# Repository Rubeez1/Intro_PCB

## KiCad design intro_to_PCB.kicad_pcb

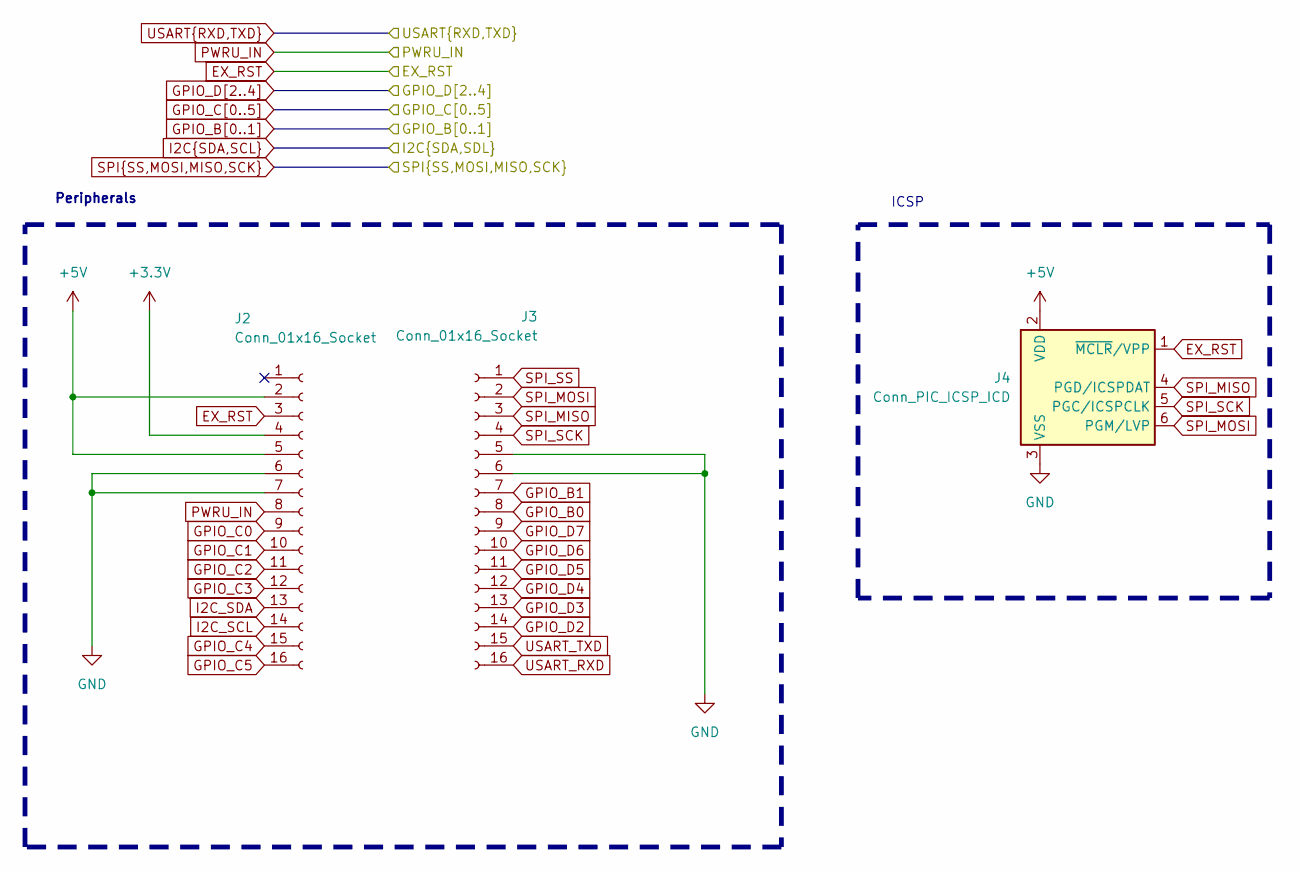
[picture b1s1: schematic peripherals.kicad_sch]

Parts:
J2, J3: Conn_01x16_Socket; PinHeader_1x16_P2.54mm_Vertical
J4: Conn_PIC_ICSP_ICD; PinHeader_2x03_P2.54mm_Vertical

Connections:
+3.3V: J2.4; also elsewhere on the board
+5V: J2.2, J2.5, J4.2 (VDD); also elsewhere on the board
EX_RST: J2.3, J4.1 (~MCLR/VPP); also elsewhere on the board
GND: J2.6, J2.7, J3.5, J3.6, J4.3 (VSS); also elsewhere on the board
GPIO_B0: J3.8; also elsewhere on the board
GPIO_B1: J3.7; also elsewhere on the board
GPIO_C0: J2.9; also elsewhere on the board
GPIO_C1: J2.10; also elsewhere on the board
GPIO_C2: J2.11; also elsewhere on the board
GPIO_C3: J2.12; also elsewhere on the board
GPIO_C4: J2.15; also elsewhere on the board
GPIO_C5: J2.16; also elsewhere on the board
GPIO_D2: J3.14; also elsewhere on the board
GPIO_D3: J3.13; also elsewhere on the board
GPIO_D4: J3.12; also elsewhere on the board
GPIO_D5: J3.11; also elsewhere on the board
GPIO_D6: J3.10; also elsewhere on the board
GPIO_D7: J3.9; also elsewhere on the board
I2C_SCL: J2.14; also elsewhere on the board
I2C_SDA: J2.13; also elsewhere on the board
PWRU_IN: J2.8; also elsewhere on the board
SPI_MISO: J3.3, J4.4 (PGD/ICSPDAT); also elsewhere on the board
SPI_MOSI: J3.2, J4.6 (PGM/LVP); also elsewhere on the board
SPI_SCK: J3.4, J4.5 (PGC/ICSPCLK); also elsewhere on the board
SPI_SS: J3.1; also elsewhere on the board
USART_RXD: J3.16; also elsewhere on the board
USART_TXD: J3.15; also elsewhere on the board

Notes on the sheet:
Peripherals
ICSP

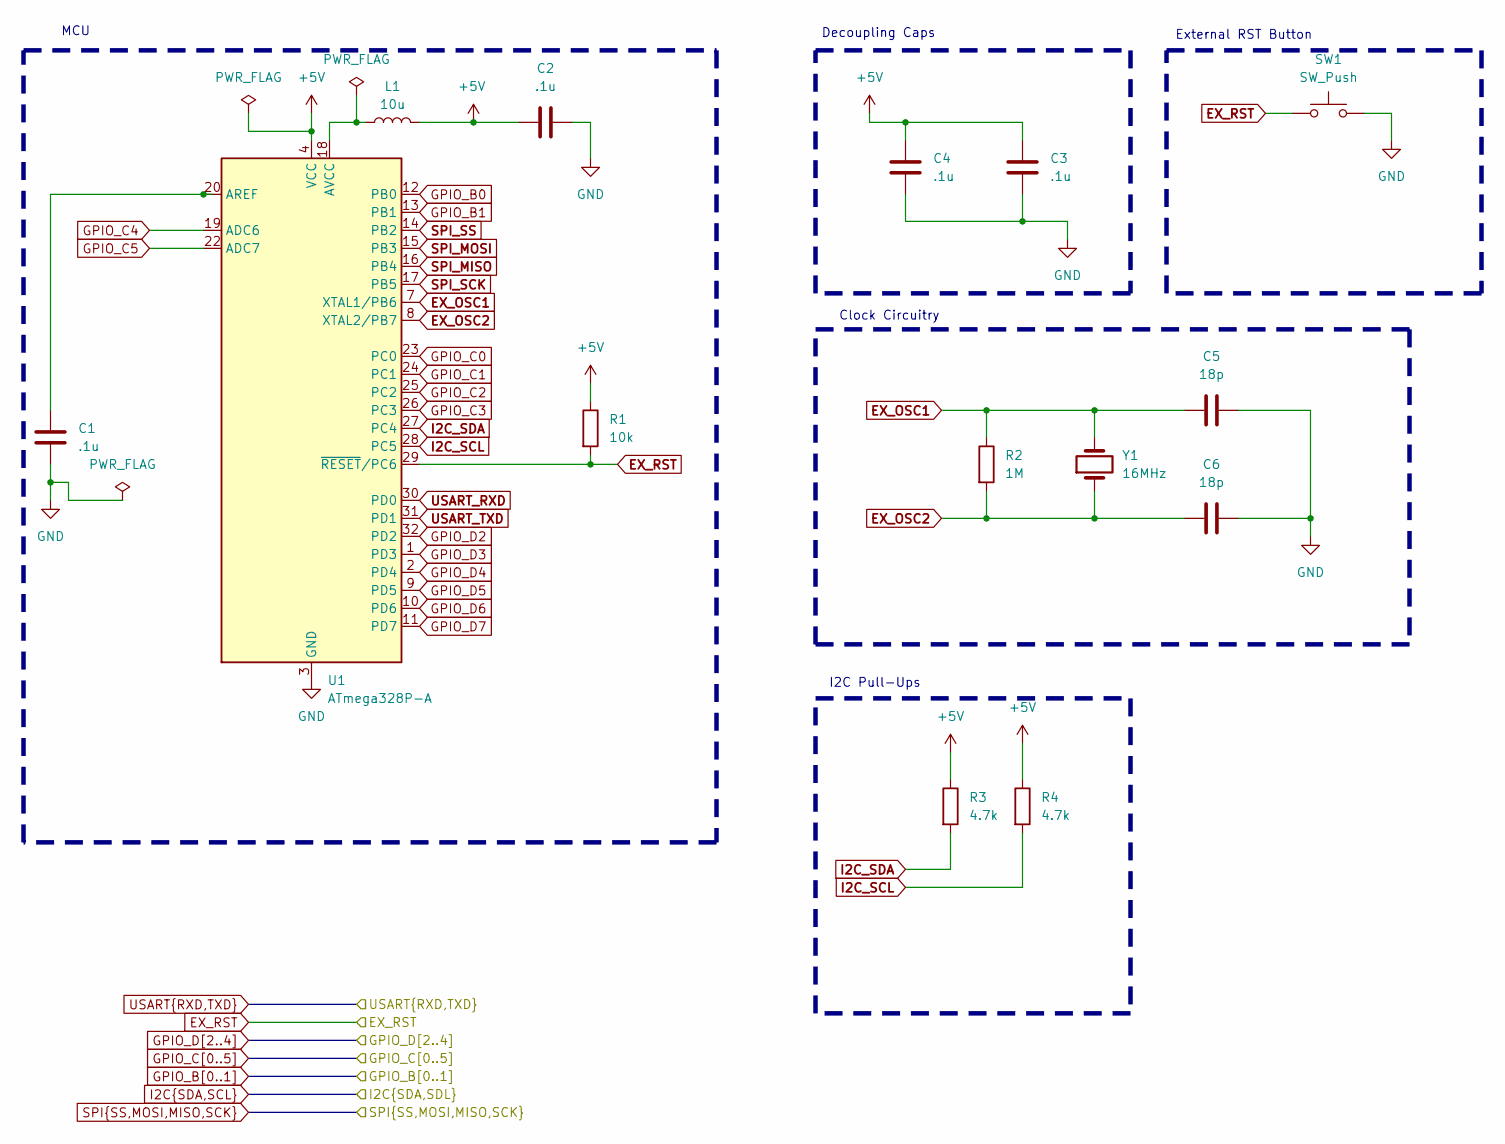
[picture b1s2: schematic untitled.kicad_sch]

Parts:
C1, C2: .1u; C_0402_1005Metric_Pad0.74x0.62mm_HandSolder
C3, C4: .1u; C_0603_1608Metric_Pad1.08x0.95mm_HandSolder
C5, C6: 18p; C_0402_1005Metric_Pad0.74x0.62mm_HandSolder
L1: 10u; L_0603_1608Metric_Pad1.05x0.95mm_HandSolder
R1: 10k; R_0402_1005Metric_Pad0.72x0.64mm_HandSolder
R2: 1M; R_0402_1005Metric_Pad0.72x0.64mm_HandSolder
R3, R4: 4.7k; R_0402_1005Metric_Pad0.72x0.64mm_HandSolder
SW1: SW_Push; SW_Push_SPST_NO_Alps_SKRK
U1: ATmega328P-A; TQFP-32_7x7mm_P0.8mm
Y1: 16MHz; Crystal_SMD_2012-2Pin_2.0x1.2mm_HandSoldering

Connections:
+5V: C2.1, C3.1, C4.1, L1.2, R1.1, R3.1, R4.1, U1.4 (VCC), U1.6 (VCC); also elsewhere on the board
EX_OSC1: C5.1, R2.1, U1.7 (XTAL1/PB6), Y1.2
EX_OSC2: C6.1, R2.2, U1.8 (XTAL2/PB7), Y1.1
EX_RST: R1.2, SW1.1, U1.29 (~RESET/PC6); also elsewhere on the board
GND: C1.2, C2.2, C3.2, C4.2, C5.2, C6.2, SW1.2, U1.3 (GND), U1.5 (GND), U1.21 (GND); also elsewhere on the board
GPIO_B0: U1.12 (PB0); also elsewhere on the board
GPIO_B1: U1.13 (PB1); also elsewhere on the board
GPIO_C0: U1.23 (PC0); also elsewhere on the board
GPIO_C1: U1.24 (PC1); also elsewhere on the board
GPIO_C2: U1.25 (PC2); also elsewhere on the board
GPIO_C3: U1.26 (PC3); also elsewhere on the board
GPIO_C4: U1.19 (ADC6); also elsewhere on the board
GPIO_C5: U1.22 (ADC7); also elsewhere on the board
GPIO_D2: U1.32 (PD2); also elsewhere on the board
GPIO_D3: U1.1 (PD3); also elsewhere on the board
GPIO_D4: U1.2 (PD4); also elsewhere on the board
GPIO_D5: U1.9 (PD5); also elsewhere on the board
GPIO_D6: U1.10 (PD6); also elsewhere on the board
GPIO_D7: U1.11 (PD7); also elsewhere on the board
I2C_SCL: R4.2, U1.28 (PC5); also elsewhere on the board
I2C_SDA: R3.2, U1.27 (PC4); also elsewhere on the board
unnamed: C1.1, U1.20 (AREF)
unnamed: L1.1, U1.18 (AVCC)
SPI_MISO: U1.16 (PB4); also elsewhere on the board
SPI_MOSI: U1.15 (PB3); also elsewhere on the board
SPI_SCK: U1.17 (PB5); also elsewhere on the board
SPI_SS: U1.14 (PB2); also elsewhere on the board
USART_RXD: U1.30 (PD0); also elsewhere on the board
USART_TXD: U1.31 (PD1); also elsewhere on the board

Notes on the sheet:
I2C Pull-Ups
External RST Button
Decoupling Caps
Clock Circuitry
MCU

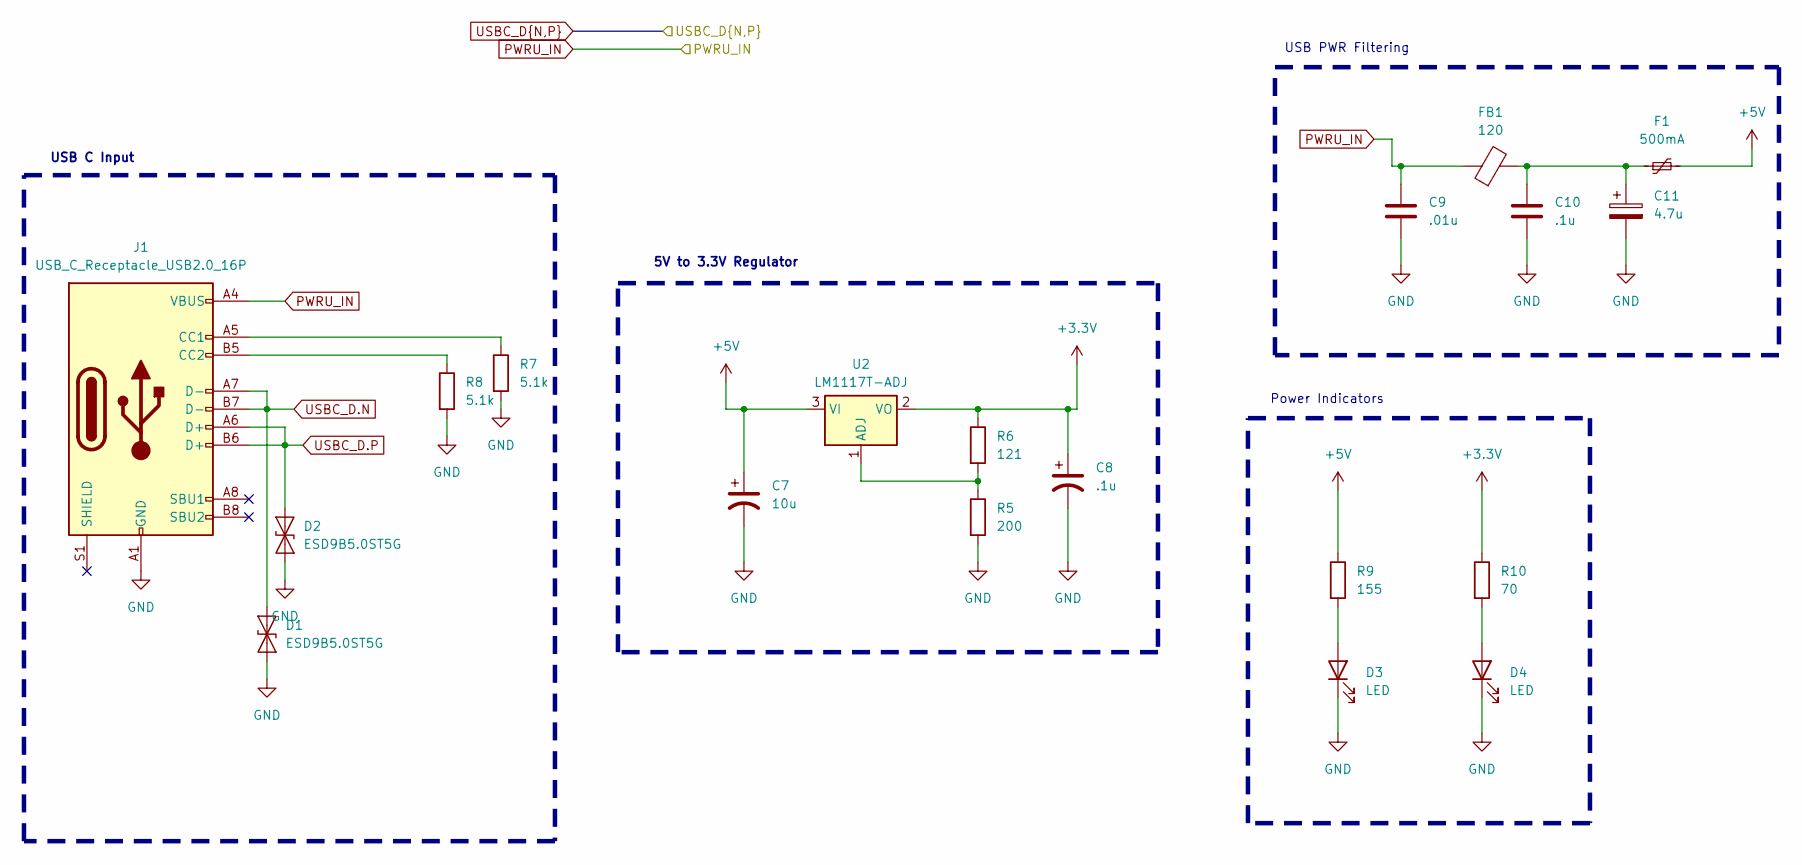
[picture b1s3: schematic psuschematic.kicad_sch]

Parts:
C7: 10u; C_Elec_6.3x7.7
C8: .1u; C_Elec_6.3x7.7
C9: .01u; C_0603_1608Metric_Pad1.08x0.95mm_HandSolder
C10: .1u; C_0603_1608Metric_Pad1.08x0.95mm_HandSolder
C11: 4.7u; C_Elec_6.3x7.7
D1, D2: ESD9B5.0ST5G; D_0402_1005Metric_Pad0.77x0.64mm_HandSolder
D3, D4: LED; D_0402_1005Metric_Pad0.77x0.64mm_HandSolder
F1: 500mA; L_1812_4532Metric_Pad1.30x3.40mm_HandSolder
FB1: 120; Fuse_0603_1608Metric_Pad1.05x0.95mm_HandSolder
J1: USB_C_Receptacle_USB2.0_16P; USB_C_Receptacle_Palconn_UTC16-G
R5: 200; R_0402_1005Metric_Pad0.72x0.64mm_HandSolder
R6: 121; R_0402_1005Metric_Pad0.72x0.64mm_HandSolder
R7, R8: 5.1k; R_0402_1005Metric_Pad0.72x0.64mm_HandSolder
R9: 155; R_0402_1005Metric_Pad0.72x0.64mm_HandSolder
R10: 70; R_0402_1005Metric_Pad0.72x0.64mm_HandSolder
U2: LM1117T-ADJ; SOT-223

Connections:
+3.3V: C8.1, R6.1, R10.1, U2.2 (VO); also elsewhere on the board
+5V: C7.1, F1.2, R9.1, U2.3 (VI); also elsewhere on the board
GND: C7.2, C8.2, C9.2, C10.2, C11.2, D1.1 (A1), D2.1 (A1), D3.1 (K), D4.1 (K), J1.A1 (GND), J1.A12 (GND), J1.B1 (GND), J1.B12 (GND), R5.2, R7.2, R8.2; also elsewhere on the board
unnamed: C10.1, C11.1, F1.1, FB1.2
unnamed: D3.2 (A), R9.2
unnamed: D4.2 (A), R10.2
unnamed: J1.A5 (CC1), R7.1
unnamed: J1.B5 (CC2), R8.1
unnamed: R5.1, R6.2, U2.1 (ADJ)
PWRU_IN: C9.1, FB1.1, J1.A4 (VBUS), J1.A9 (VBUS), J1.B4 (VBUS), J1.B9 (VBUS); also elsewhere on the board
USBC_D.N: D1.2 (A2), J1.A7 (D-), J1.B7 (D-); also elsewhere on the board
USBC_D.P: D2.2 (A2), J1.A6 (D+), J1.B6 (D+); also elsewhere on the board

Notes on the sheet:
Power Indicators
USB C Input
USB PWR Filtering
5V to 3.3V Regulator

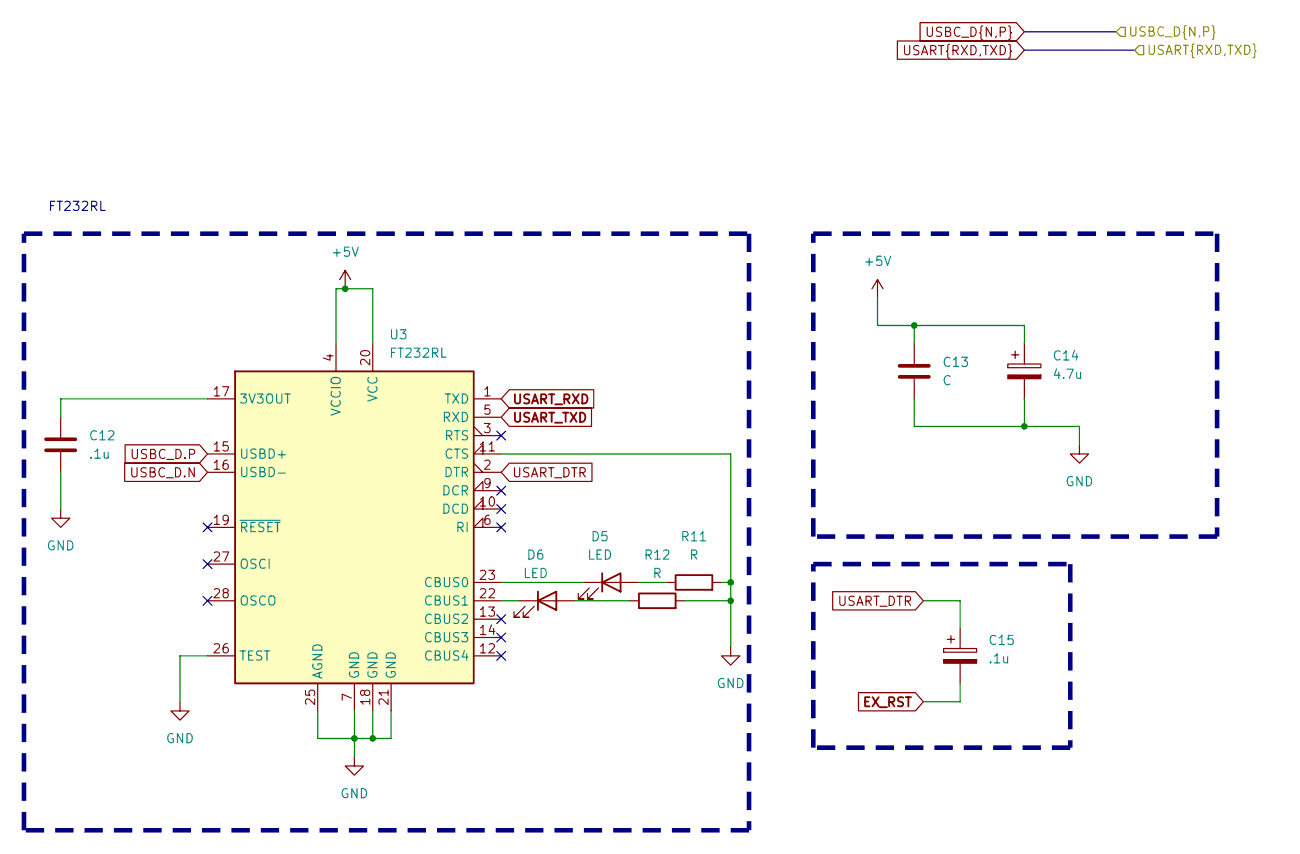
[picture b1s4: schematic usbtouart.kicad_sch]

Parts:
C12: .1u; C_0402_1005Metric_Pad0.74x0.62mm_HandSolder
C13: C; C_0603_1608Metric_Pad1.08x0.95mm_HandSolder
C14: 4.7u; C_Elec_6.3x7.7
C15: .1u; C_Elec_6.3x7.7
D5, D6: LED; D_0402_1005Metric_Pad0.77x0.64mm_HandSolder
R11, R12: R; R_0402_1005Metric_Pad0.72x0.64mm_HandSolder
U3: FT232RL; SSOP-28_5.3x10.2mm_P0.65mm

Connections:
+5V: C13.1, C14.1, U3.4 (VCCIO), U3.20 (VCC); also elsewhere on the board
EX_RST: C15.2; also elsewhere on the board
GND: C12.2, C13.2, C14.2, R11.2, R12.2, U3.7 (GND), U3.11 (CTS), U3.18 (GND), U3.21 (GND), U3.25 (AGND), U3.26 (TEST); also elsewhere on the board
unnamed: D5.2 (A), R11.1
unnamed: D5.1 (K), U3.23 (CBUS0)
unnamed: D6.2 (A), R12.1
unnamed: D6.1 (K), U3.22 (CBUS1)
unnamed: C12.1, U3.17 (3V3OUT)
USART_DTR: C15.1, U3.2 (DTR)
USART_RXD: U3.1 (TXD); also elsewhere on the board
USART_TXD: U3.5 (RXD); also elsewhere on the board
USBC_D.N: U3.16 (USBD-); also elsewhere on the board
USBC_D.P: U3.15 (USBD+); also elsewhere on the board

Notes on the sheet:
FT232RL

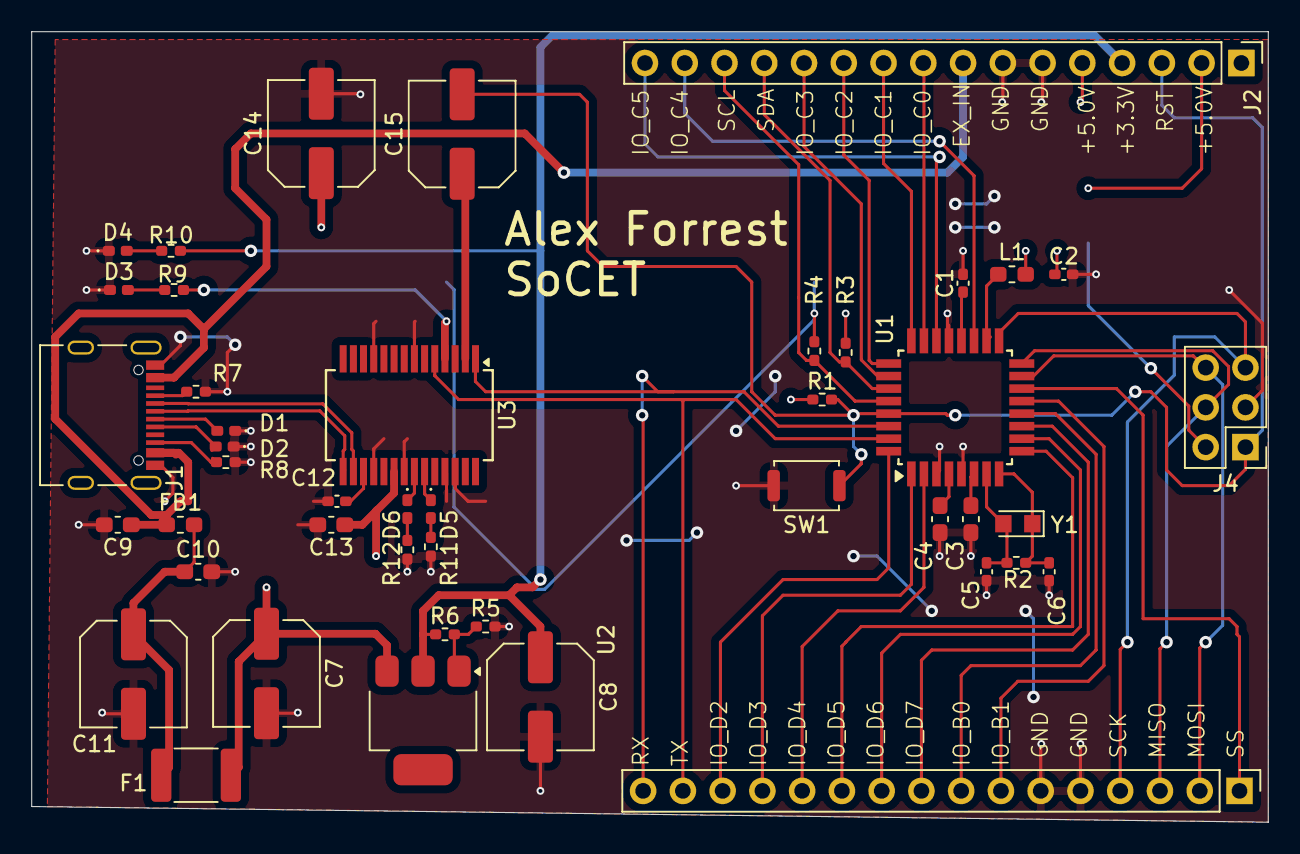
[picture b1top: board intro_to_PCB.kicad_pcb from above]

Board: 2 copper layers, 79.0 x 50.5 mm, 45 parts (0 on the bottom side), 45 nets.

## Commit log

2025-02-10 final intro pcb
2025-02-11 fixed clearance
